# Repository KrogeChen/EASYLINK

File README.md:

# TOPOLOGY

FAlink----------------------------------------------------------------------------------------------------------------(Max..30)
            |               |                   |                               |                             |
    		|          		|             		|                          		|                         	  |
    		|          		|             		|                          		|                         	  |
    	|-------|      	|-------|         	|--------|                     	|--------|                    |--------|
    	| NODE  |      	| NODE  |         	|NODE(EX)|                     	|NODE(EX)|                    |NODE(WL)|
    	|-------|      	|-------|         	|--------|                    	|--------|                    |--------|
    	                                     WIRELESS                        WIRELESS                        MQTT
    		           		              		.                           	.                              @
    											.                    			.                              @
    									.................            	.................                 %%%%%%%%%%
    									.     	        .            	.     	        .                 % REMOTE %
    									.               .            	.               .                 % SERVER %
    								|--------|     |---------|      |--------|     |---------|            %%%%%%%%%%
    							    | SENSER |	   | SENSER  |      | LINKAGE|     | LINKAGE |              	
    		                        |--------|     |---------|      |--------|     |---------|              
    
注:每个节点分配64bit(8byte)的虚拟ID

# EASYLINK
easy link protocol by cdbus

承担任务:
1、帧同步、寻址控制
2、数据的发送流、接收流
3、数据的差错控制
4、数据的流量管控
5、帧冲突管理

源地址|目标地址|长度|报文类型 |报文负载|校验
  SRC    DST    LEN     TPE      PAY    FCS
   1      1      1       1        n      2

LEN  帧长度  TPE+PAY的字节数
FCS  CRC16   由PHY芯片自动完毕。

//--------------------------------------------------------------------------------------------------
//特殊地址分配
//0x20 租约中心地址
//0xF0--0xFE 空地址
//0xFF 广播地址
//++++++++++++++++++++++++++++++++++++++++++++++++++++++++++++++++++++++++++++++++++++++++++++++++++
//++++++++++++++++++++++++++++++++++++++++++++++++++++++++++++++++++++++++++++++++++++++++++++++++++
# NETWORK

## ELAP 地址租约，

承担任务:
1、数据链路层的节点地址分配
2、虚拟ID和节点地址关联的租约表
3、生成64bit的网络随机标识
3、子集管理，扩展MAP管理

TPE: 0x01 地址租约服务
租约中心(地址:0x20)
首租流程
续租流程
租约中心申请流程

上电-->首租-->首租请求报文，SRC 0xFE DST 0x01-->租约中心应答-->获取租期和地址-->确认租约-->完毕
                                             -->租约中心无应答-->重试3次-->申请为租约中心
    -->续租-->续租请求报文，SRC 0xFE DST 0x01

    -->发布租约中心公告3次-->无冲突反馈-->正式成为租约中心,赋地址0x20
                          -->有冲突反馈-->退出租约中心申请-->进入地址租赁申请流程
//--------------------------------------------------------------------------------------------------
消息ID  命令   虚拟ID    节点地址
 MSGID  CMD     VUID      NADDR  
   2     1       8          1     
//--------------------------------------------------------------------------------------------------
CMD1:0x01 首租请求
		  35 AE | 01 | 89 76 73 87 AE 83 78 4A AE 83 78 4A | FE
		  
	 0x81 请求应答	  
          35 AE | 81 | 89 76 73 87 AE 83 78 38 AE 83 78 4A | 03	
		  
	 0xA1 租约失败,(一般是系统地址容量已满)
          35 AE | A1 | 89 76 73 87 AE 83 78 38 AE 83 78 4A | FE
		  
	 0xC1 租约确认
          35 AE | C1 | 89 76 73 87 AE 83 78 4A AE 83 78 4A | 03

CMD2:0x02 续租请求  
          35 AE | 02 | 89 76 73 87 AE 83 78 4A AE 83 78 4A | 03
		  
	 0x82 请求应答	  
          35 AE | 82 | 89 76 73 87 AE 83 78 38 AE 83 78 4A | 03	
		  
	 0xA2 租约失败,(一般是地址冲突)
          35 AE | A2 | 89 76 73 87 AE 83 78 38 AE 83 78 4A | 03

	 0xC2 租约确认
          35 AE | C2 | 89 76 73 87 AE 83 78 4A AE 83 78 4A | 03

CMD3:0x03 租约中心公告,
          空地址时,10秒内公告5次,无应答,本机成为租约中心,获得0x20地址。
          已经成为租约中心,每2小时,公告一次,1秒内连续发送3个报文。
          03 48 | 01 | 89 76 73 87 AE 83 78 31 AE 83 78 31 | FF
		  03 48 | 01 | 89 76 73 87 AE 83 78 31 AE 83 78 31 | 01
		                       本机ID

     0x83 公告应答,收到应答,租约中心冲突,放弃成为租约中心。
	      03 48 | 81 | 89 76 73 87 AE 83 78 38 AE 83 78 39 | FF

CMD4:0x04 地址和ID的关系表发布,ID MAP按序列排布,地址隐含表达,一个报文241byte,30个节点Id,1个字节的地址偏移

CMD5:0x05 扩展ID MAP发布,由NODE(EX)节点发布到总线上面,管理无线设备子集

格式: 消息ID  命令
       MSGID  CMD
         2     1 
CMD4:0x04 租约表请求
       03 48 | 04 | 

格式: 消息ID  命令  节点数量       节点表      
       MSGID  CMD     NODE      [NADDR+VUID] ... 
         2     1       1           1    12  
CMD5:0x05 租约表公布
       03 48 | 05 | 03 | 01 | 89 76 73 87 AE 83 78 31 AE 83 78 31 | 02 | 89 76 73 87 AE 83 78 31 AE 83 78 32 | 03 | 89 76 73 87 AE 83 78 31 AE 83 78 35 

CMD6:0x06 扩展备案

CMD7:0x07 扩展表公布

CMD16: 0x10 获取VUID命令,返回设备的VUID
//++++++++++++++++++++++++++++++++++++++++++++++++++++++++++++++++++++++++++++++++++++++++++++++++++
##EOTA 固件升级
TPE: 0x02 固件升级

开始 --> 接受到触发升级的信号及"固件资源位置"

     --> 向"固件资源位置"请求文件

     --> BOOT状态 -->发送升级数据包-->END
//--------------------------------------------------------------------------------------------------
KV值 KEY-VALUE 文件的关键标识 64BIT

格式: 消息ID  命令  状态   资源位置   
       MSGID  CMD   STU   VUID + FLKV
         2     1     1      8     12  
CMD1: 0x01 触发升级
           03 48 | 01 | FF |89 76 73 87 AE 83 78 31 AE 83 78 39 | 34 D3 81 47 E3 4D 71 30
		
      0x81  应答
	       03 48 | 81 | FF |89 76 73 87 AE 83 78 31 AE 83 78 39 | 34 D3 81 47 E3 4D 71 30

格式: 消息ID   命令  状态       资源KV   块序列   块内容(请求时内容为空)
       MSGID   CMD   STU         FLKV    BKSEQ    DETAILS
         2      1     1           12        2        128	
CMD2:0x02  传输请求
          03 48 | 02 | FF |34 D3 81 47 E3 4D 71 30 | 00 00 
		  
	 0x82  传输应答
	      03 48 | 82 | FF |34 D3 81 47 E3 4D 71 30 | 00 00 |93 94 ..(128B).. 23 54
		  
     0xA2  错误报告
          03 48 | A2 | FE |34 D3 81 47 E3 4D 71 30 | 00 00 
		  
		  需要设计OTA报文传输间隔 ms
CMD3:0x03  连续报文传输请求
状态码:
     0x00 填充
	 0xFD 块请求超出文件范围
	 0xFE 未知错误
	 0xFF 填充

//----------------------------------------------------------------------------------------------------

//++++++++++++++++++++++++++++++++++++++++++++++++++++++++++++++++++++++++++++++++++++++++++++++++++

TPE: 0x03 公告发布,节点数据发布
          节点关联列表

		  联动状态
		  
		  资源方数据点,AAAAAAAABBBBBBBB.23
		  联动方数据点,CCCCCCCCDDDDDDDD.02

//++++++++++++++++++++++++++++++++++++++++++++++++++++++++++++++++++++++++++++++++++++++++++++++++++
TPE: 0x04 控制数据点传输
     格式:  消息ID | 命令  | 数据点归属UID |数据点序列 |
	           2       1        ...
	 CMD1:   0x01  数据广播发布,无需应答,至多到达一次
	 CMD2:   0x02  数据单播发布,需要应答,至少到达一次 
	 CMD3:   0x03  数据写入,需要应答,至少到达一次 

	 CMD4:   0x04  数据读取,需要应答
	 
     格式:  消息ID | 命令  |  数据点数量 | 数据点内容 |
	           2       1          1           ...
	 CMD5:   0x05  数据写读,写入目标设备数据点的同时,读取目标设备的数据点
	 
//++++++++++++++++++++++++++++++++++++++++++++++++++++++++++++++++++++++++++++++++++++++++++++++++++
TPE: 0x10 控制数据传输协议(是否直接采用字符传输？？)
                                   
  1 	  1       2    8        8          1                8				
|版本|异常报告|保留|源UID | 目标UID | 命令.请求PID     | 归属UID |
		            源UID | 目标UID | 命令.请求PID应答 | 归属UID |PID |
		                                                
														SOFTVER
														
														HARDVER
		  
		                  | 命令.请求数据点  | 归属UID |数据点ID  |
                                   REPLY     | 归属UID |数据点序列|
											 
                          | 命令.修改数据点  | 归属UID |数据点序列|
                                             | 归属UID |改后的数据序列|
											 
                          | 命令.上报数据点  | 归属UID |数据点序列|										   

	  数据点序列排布方法
	  ${数据点ID}{DP长度}{DP内容}{数据点ID}{DP长度}{DP内容}....
	       1         1     VAR       1         1     VAR
//++++++++++++++++++++++++++++++++++++++++++++++++++++++++++++++++++++++++++++++++++++++++++++++++++
资源定位方式
//++++++++++++++++++++++++++++++++++++++++++++++++++++++++++++++++++++++++++++++++++++++++++++++++++
消息服务质量
QoS 0: 消息至多传送 1 次。
QoS 1: 消息至少传送 1 次。
QoS 2: 消息仅仅传送 1 次。

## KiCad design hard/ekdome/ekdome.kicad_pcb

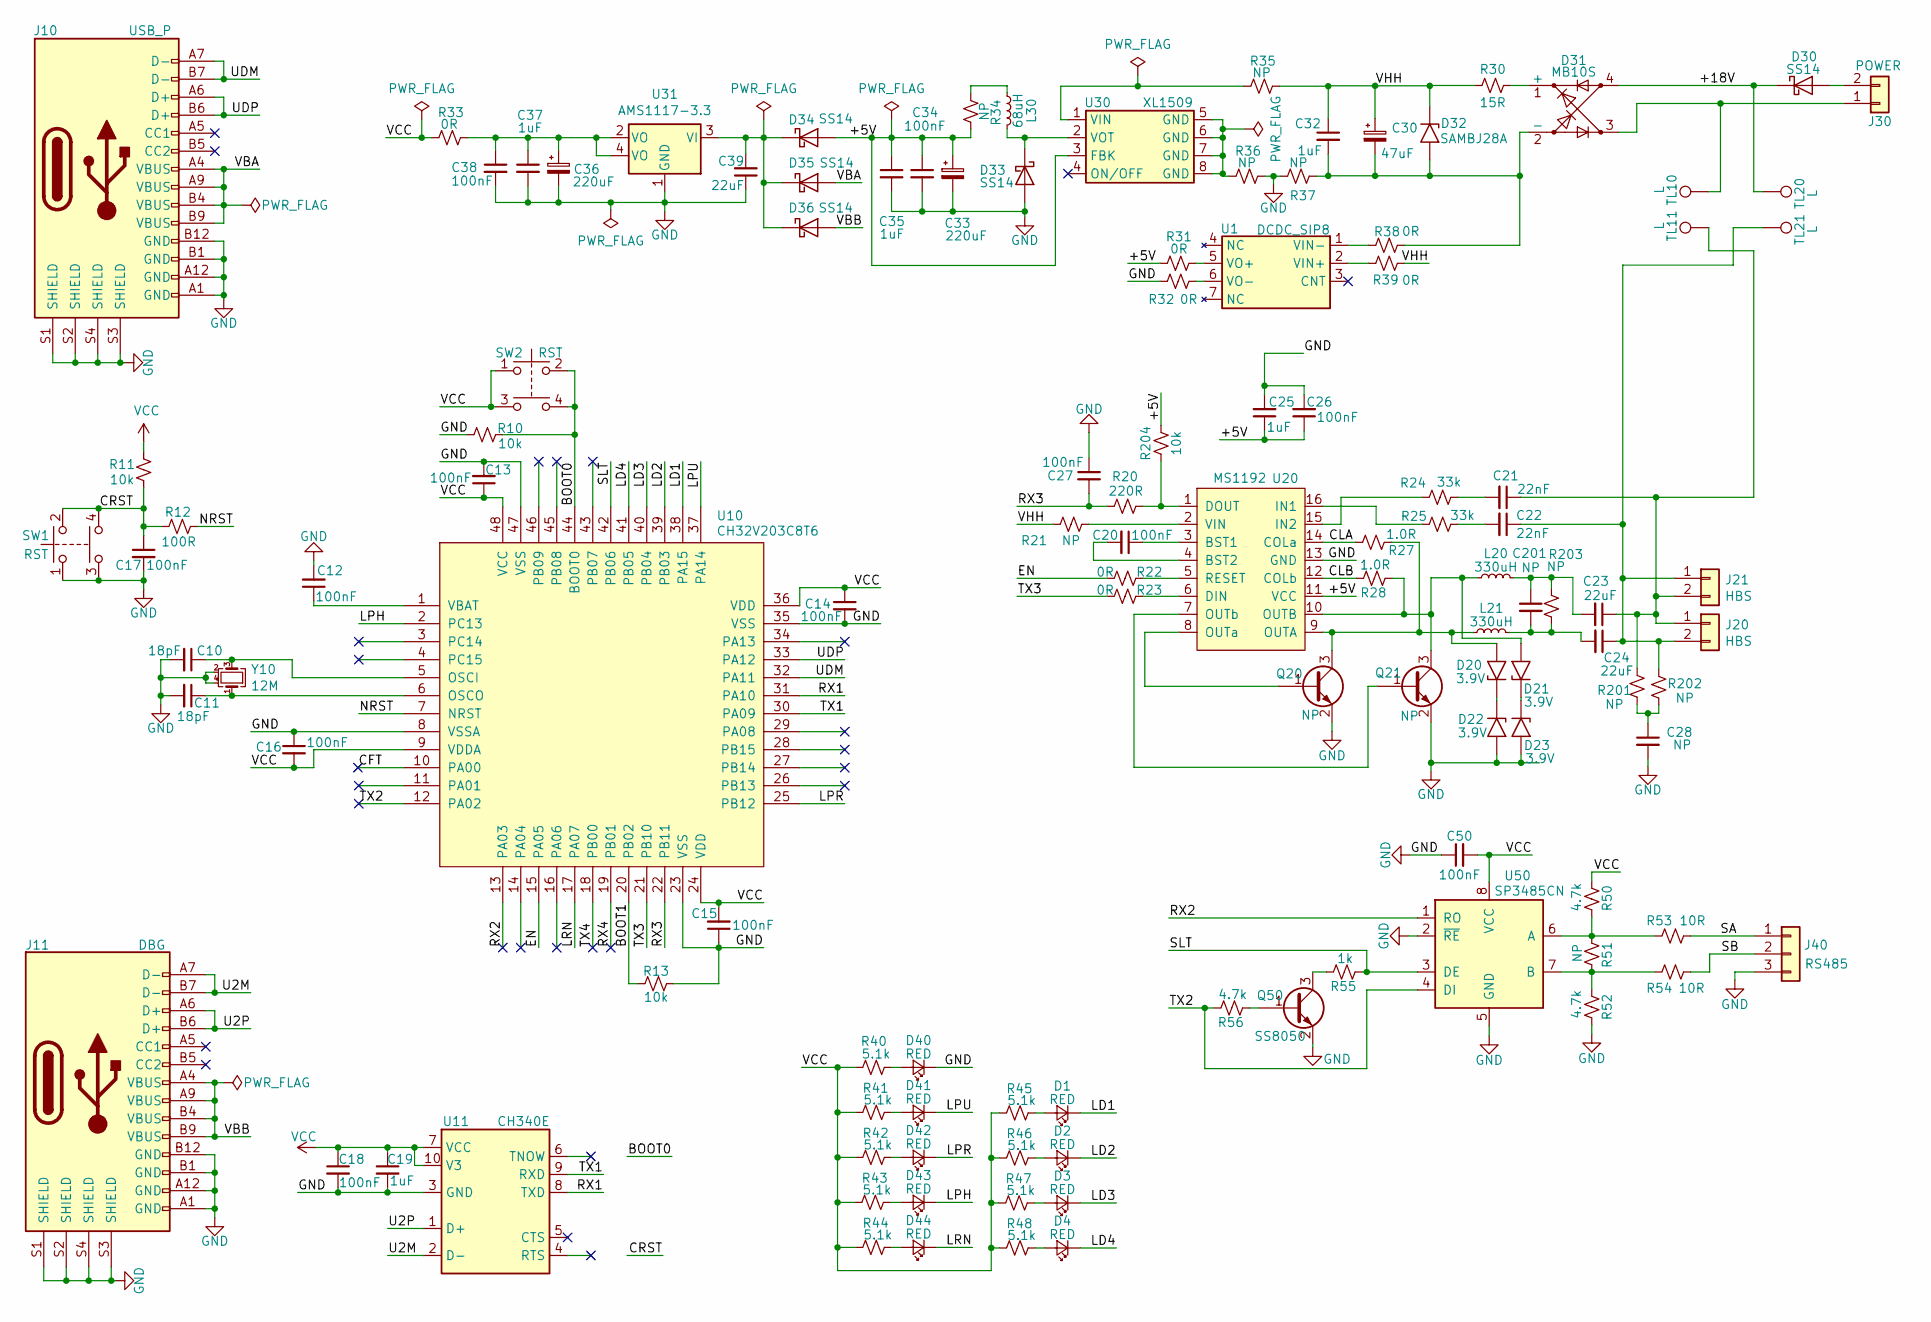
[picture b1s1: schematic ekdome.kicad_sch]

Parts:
C10, C11: 18pF; C_0603_1608Metric
C12, C13, C14, C15, C16, C17, C18, C20, C26, C27, C34, C38, C50: 100nF; C_0603_1608Metric
C19, C25, C35, C37: 1uF; C_0603_1608Metric
C21, C22: 22nF; C_0603_1608Metric
C23, C24: 22uF; CP_Elec_6.3x5.4
C28: NP; C_1206_3216Metric
C30: 47uF; CP_Elec_8x6.5
C32: 1uF; C_0805_2012Metric
C33, C36: 220uF; CP_Elec_6.3x5.4
C39: 22uF; C_1206_3216Metric
C201: NP; C_0603_1608Metric
D1, D2, D3, D4, D40, D41, D42, D43, D44: RED; LED_0603_1608Metric
D20, D21, D22, D23: 3.9V; D_SOD-123F
D30, D33, D34, D35, D36: SS14; D_SMA
D31: MB10S; Diode_Bridge_MB10S
D32: SAMBJ28A; D_SMB
J10: USB_P; USB_C_Receptacle_14Pin
J11: DBG; USB_C_Receptacle_14Pin
J20, J21: HBS; PhoenixContact_MCV_1,5_2-G-3.81_1x02_P3.81mm_Vertical
J30: POWER; PhoenixContact_MCV_1,5_2-G-3.81_1x02_P3.81mm_Vertical
J40: RS485; PhoenixContact_MCV_1,5_3-G-3.81_1x03_P3.81mm_Vertical
L20, L21: 330uH; L_Bourns-SRN4018
L30: 68uH; L_Bourns_SRN6045TA
Q20, Q21: NP; SOT-23
Q50: SS8050; SOT-23
R10, R11, R13, R204: 10k; R_0603_1608Metric
R12: 100R; R_0603_1608Metric
R20: 220R; R_0603_1608Metric
R21, R201, R202: NP; R_1206_3216Metric
R22, R23: 0R; R_0603_1608Metric
R24, R25: 33k; R_0603_1608Metric
R27, R28: 1.0R; R_0603_1608Metric
R30: 15R; R_Axial_DIN0411_L9.9mm_D3.6mm_P18mm_Horizontal
R31, R32, R33, R38, R39: 0R; R_0805_2012Metric
R34, R35, R36, R37: NP; R_0805_2012Metric
R40, R41, R42, R43, R44, R45, R46, R47, R48: 5.1k; R_0603_1608Metric
R50, R52, R56: 4.7k; R_0603_1608Metric
R51, R203: NP; R_0603_1608Metric
R53, R54: 10R; R_1206_3216Metric
R55: 1k; R_0603_1608Metric
SW1, SW2: RST; SW_KAN0541
TL10, TL11, TL20, TL21: L; TestPoint_Loop_D2.50mm_Drill1.0mm
U1: DCDC_SIP8; TDKSIP8
U10: CH32V203C8T6; LQFP-48_7x7mm_P0.5mm
U11: CH340E; MSOP-10_3x3mm_P0.5mm
U20: MS1192; SOIC-16_3.9x9.9mm_P1.27mm
U30: XL1509; SOIC-8_3.9x4.9mm_P1.27mm
U31: AMS1117-3.3; SOT-223
U50: SP3485CN; SOIC-8_3.9x4.9mm_P1.27mm
Y10: 12M; Crystal_SMD_3225-4Pin_3.2x2.5mm

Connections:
/+5V: C25.1, C26.1, C33.1, C34.1, C35.1, D34.2 (A), R31.1, R34.2, R204.1, U20.11 (VCC), U30.3 (FBK)
/+18V: D30.1 (K), D31.4, TL20.1
/BOOT0: R10.2, SW2.2, SW2.4, U10.44 (BOOT0)
/BOOT1: R13.1, U10.20 (PB02)
/CFT: U10.10 (PA00)
/CLA: R27.2, U20.14 (COLa)
/CLB: R28.2, U20.12 (COLb)
/CRST: C17.1, R11.1, R12.1, SW1.2, SW1.4
/EN: R22.2, U10.15 (PA05)
/LD1: D1.1 (K), U10.38 (PA15)
/LD2: D2.1 (K), U10.39 (PB03)
/LD3: D3.1 (K), U10.40 (PB04)
/LD4: D4.1 (K), U10.41 (PB05)
/LPH: D43.1 (K), U10.2 (PC13)
/LPR: D42.1 (K), U10.25 (PB12)
/LPU: D41.1 (K), U10.37 (PA14)
/LRN: D44.1 (K), U10.17 (PA07)
/NRST: R12.2, U10.7 (NRST)
/RX1: U10.31 (PA10), U11.8 (TXD)
/RX2: U10.13 (PA03), U50.1 (RO)
/RX3: C27.2, R20.2, U10.22 (PB11)
/RX4: U10.19 (PB01)
/SA: J40.1, R53.2
/SB: J40.2, R54.2
/SLT: R55.1, U10.42 (PB06), U50.3 (DE)
/TX1: U10.30 (PA09), U11.9 (RXD)
/TX2: R56.2, U10.12 (PA02), U50.4 (DI)
/TX3: R23.2, U10.21 (PB10)
/TX4: U10.18 (PB00)
/U2M: J11.A7 (D-), J11.B7 (D-), U11.2 (D-)
/U2P: J11.A6 (D+), J11.B6 (D+), U11.1 (D+)
/UDM: J10.A7 (D-), J10.B7 (D-), U10.32 (PA11)
/UDP: J10.A6 (D+), J10.B6 (D+), U10.33 (PA12)
/VBA: D35.2 (A), J10.A4 (VBUS), J10.A9 (VBUS), J10.B4 (VBUS), J10.B9 (VBUS)
/VBB: D36.2 (A), J11.A4 (VBUS), J11.A9 (VBUS), J11.B4 (VBUS), J11.B9 (VBUS)
/VHH: C30.1, C32.1, D32.1 (A1), R21.2, R30.2, R35.2, R39.2
GND: C10.2, C11.2, C12.2, C13.2, C14.2, C15.1, C16.1, C17.2, C18.2, C19.2, C25.2, C26.2, C27.1, C28.2, C33.2, C34.2, C35.2, C36.2, C37.2, C38.2, C39.1, C50.1, D22.2 (A2), D23.2 (A2), D33.2 (A), D40.1 (K), J10.A1 (GND), J10.A12 (GND), J10.B1 (GND), J10.B12 (GND), J10.S1 (SHIELD), J10.S2 (SHIELD), J10.S3 (SHIELD), J10.S4 (SHIELD), J11.A1 (GND), J11.A12 (GND), J11.B1 (GND), J11.B12 (GND), J11.S1 (SHIELD), J11.S2 (SHIELD), J11.S3 (SHIELD), J11.S4 (SHIELD), J40.3, Q20.2 (E), Q21.2 (E), Q50.2 (E), R10.1, R13.2, R32.1, R36.2, R37.1, R52.2, SW1.1, SW1.3, U10.8 (VSSA), U10.23 (VSS), U10.35 (VSS), U10.47 (VSS), U11.3 (GND), U20.13 (GND), U31.1 (GND), U50.2 (~RE), U50.5 (GND), Y10.2, Y10.4
unnamed: C21.2, R24.1
unnamed: C22.2, R25.1
unnamed: C28.1, R201.2, R202.2
unnamed: C36.1, C37.1, C38.1, R33.2, U31.2 (VO), U31.4 (VO)
unnamed: C23.2, C201.1, L20.2, R203.1
unnamed: C24.2, C201.2, L21.2, R203.2
unnamed: D1.2 (A), R45.2
unnamed: D2.2 (A), R46.2
unnamed: D3.2 (A), R47.2
unnamed: D4.2 (A), R48.2
unnamed: D20.1 (A1), D22.1 (A1)
unnamed: D20.2 (A2), L21.1, Q20.3 (C), R27.1, U20.9 (OUTA)
unnamed: D21.1 (A1), D23.1 (A1)
unnamed: D21.2 (A2), L20.1, Q21.3 (C), R28.1, U20.10 (OUTB)
unnamed: D30.2 (A), J30.2
unnamed: D31.1 (+), R30.1
unnamed: C30.2, C32.2, D31.2 (-), D32.2 (A2), R37.2, R38.2
unnamed: D33.1 (K), L30.2, U30.2 (VOT)
unnamed: C39.2, D34.1 (K), D35.1 (K), D36.1 (K), U31.3 (VI)
unnamed: D40.2 (A), R40.2
unnamed: D41.2 (A), R41.2
unnamed: D42.2 (A), R42.2
unnamed: D43.2 (A), R43.2
unnamed: D44.2 (A), R44.2
unnamed: C21.1, C23.1, J20.1, J21.2, R201.1, TL11.1
unnamed: C22.1, C24.1, J20.2, J21.1, R202.1, TL21.1
unnamed: D31.3, J30.1, TL10.1
unnamed: L30.1, R34.1
unnamed: Q20.1 (B), U20.8 (OUTa)
unnamed: Q21.1 (B), U20.7 (OUTb)
unnamed: Q50.1 (B), R56.1
unnamed: Q50.3 (C), R55.2
unnamed: R36.1, U30.5 (GND), U30.6 (GND), U30.7 (GND), U30.8 (GND)
unnamed: R39.1, U1.2 (VIN+)
unnamed: R38.1, U1.1 (VIN-)
unnamed: R31.2, U1.5 (VO+)
unnamed: R32.2, U1.6 (VO-)
unnamed: C10.1, U10.5 (OSCI), Y10.3
unnamed: C11.1, U10.6 (OSCO), Y10.1
unnamed: C12.1, U10.1 (VBAT)
unnamed: C20.1, U20.3 (BST1)
unnamed: C20.2, U20.4 (BST2)
unnamed: R23.1, U20.6 (DIN)
unnamed: R20.1, R204.2, U20.1 (DOUT)
unnamed: R25.2, U20.16 (IN1)
unnamed: R24.2, U20.15 (IN2)
unnamed: R22.1, U20.5 (RESET)
unnamed: R21.1, U20.2 (VIN)
unnamed: R35.1, U30.1 (VIN)
unnamed: R50.2, R51.1, R53.1, U50.6 (A)
unnamed: R51.2, R52.1, R54.1, U50.7 (B)
VCC: C13.1, C14.1, C15.2, C16.2, C18.1, C19.1, C50.2, R11.2, R33.1, R40.1, R41.1, R42.1, R43.1, R44.1, R45.1, R46.1, R47.1, R48.1, R50.1, SW2.1, SW2.3, U10.9 (VDDA), U10.24 (VDD), U10.36 (VDD), U10.48 (VCC), U11.7 (VCC), U11.10 (V3), U50.8 (VCC)

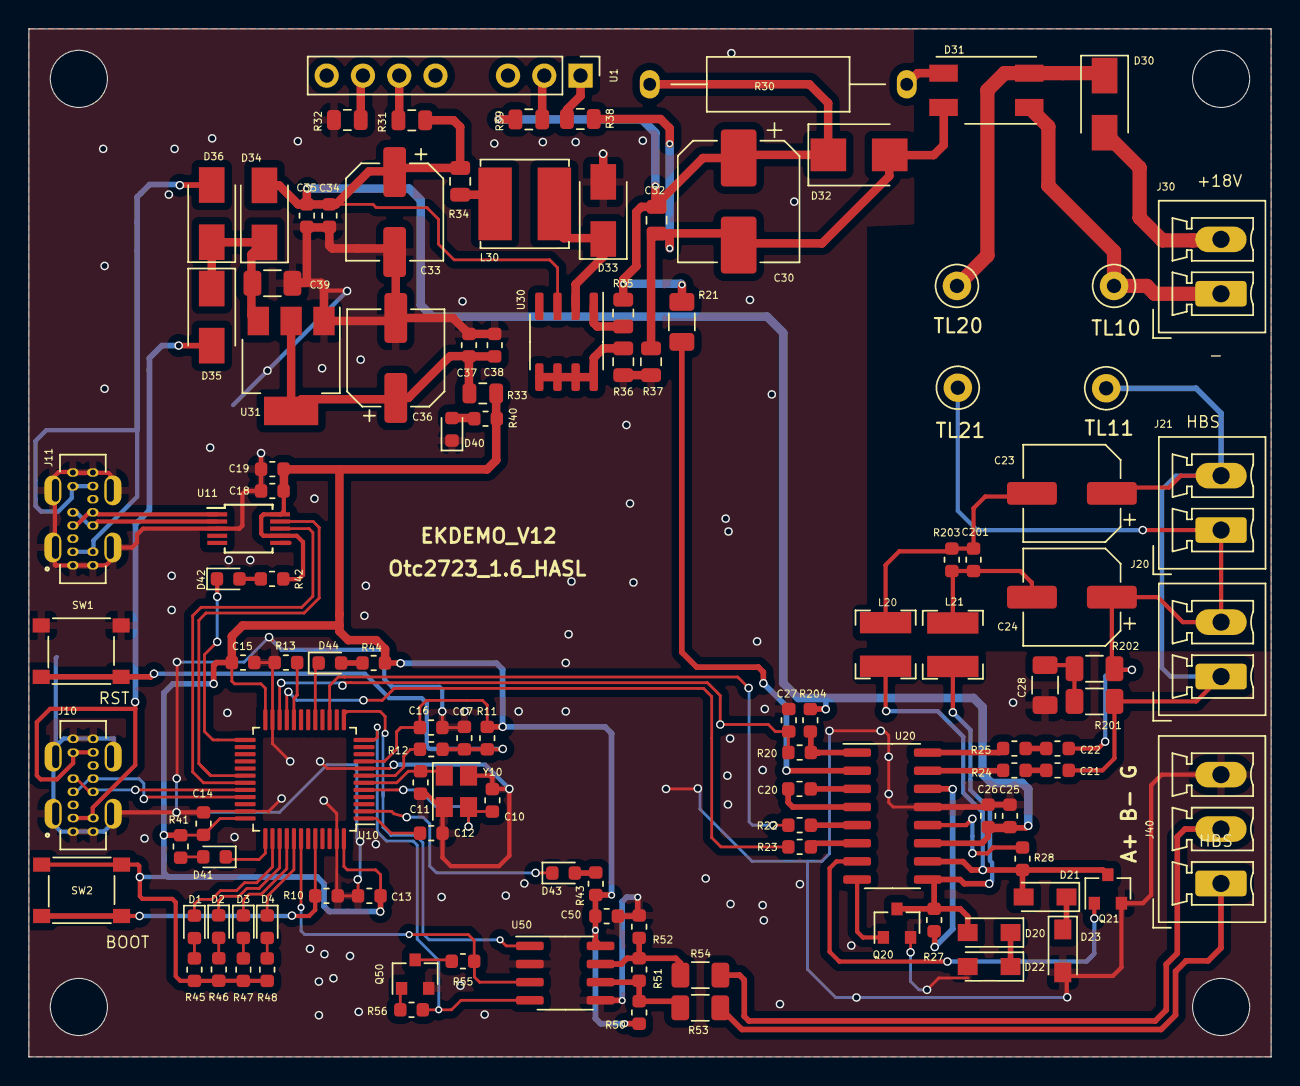
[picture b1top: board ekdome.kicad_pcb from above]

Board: 2 copper layers, 87.0 x 72.0 mm, 118 parts (0 on the bottom side), 86 nets.

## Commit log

2022-11-17 add a homebus repeat designed
2022-12-08 ekdome schematic is designed.
2022-12-08 start pcb layout
2022-12-10 EK DEMO is designed. it is gone to JLC process.
2023-02-26 add some chip data sheet
2023-05-30 start edit software
2023-05-31 system can run
2023-06-06 sch modify
2023-06-09 V1.1 complete
2023-06-14 add ECHONET sepc
2023-08-17 自动地址分配，固件请求规划
2023-08-23 modify
2023-08-23 add network layer
2023-08-23 modify some mark
2023-08-30 add checksum
2023-08-31 add debug app file
2023-09-11 usart send module is complete
2023-09-13 debug rxd code
2023-09-13 trx debug version
2023-09-15 add pilot light module
2023-09-16 link data add shun back fun
2023-10-28 增加485端口用于协议调试
2024-02-03 test commit
2024-03-21 add some think
2024-03-22 add match link code
2024-03-26 layout of text draw
2024-04-09 resource and link add
2024-09-18 Falink初稿协议位置
